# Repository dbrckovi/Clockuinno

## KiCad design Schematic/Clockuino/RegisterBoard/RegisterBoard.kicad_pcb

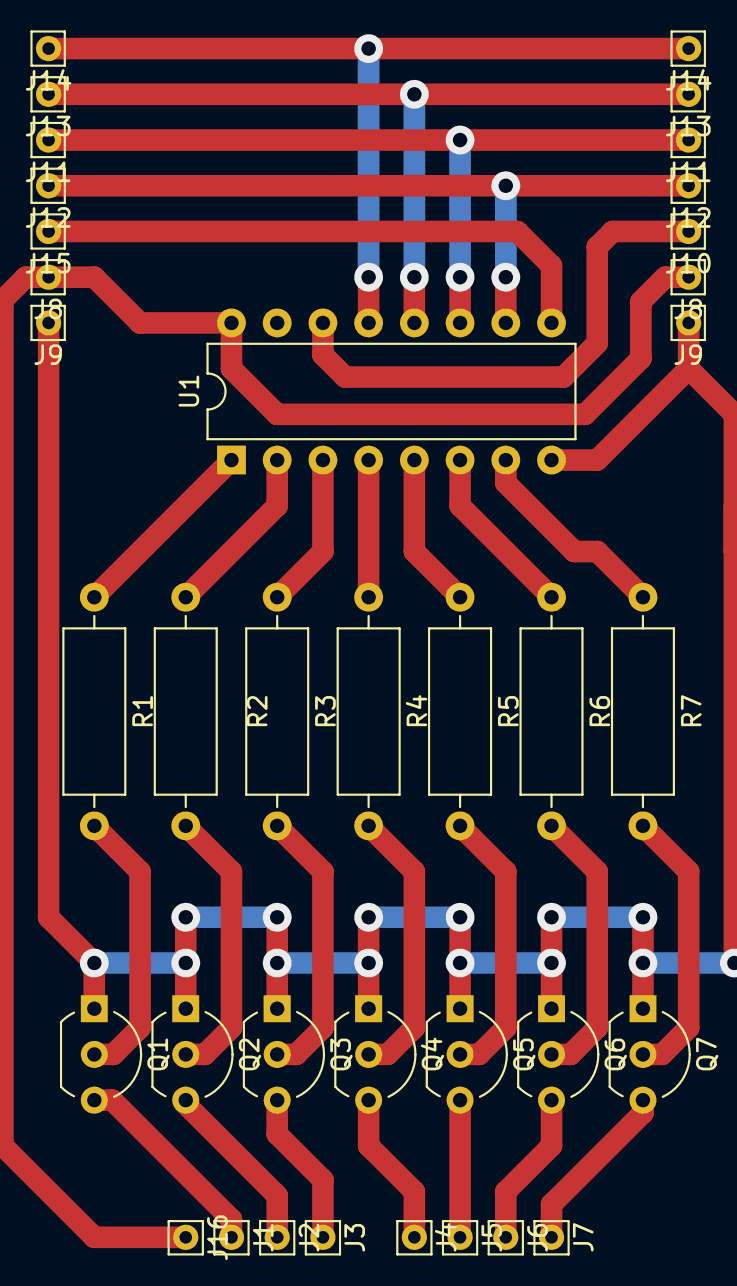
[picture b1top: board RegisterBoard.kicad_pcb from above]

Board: 2 copper layers, 37 parts (0 on the bottom side), 29 nets.

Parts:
J1, J2, J3, J4, J5, J6, J7: Conn_01x01_Pin; Pin_D0.7mm_L6.5mm_W1.8mm_FlatFork
J8, J8#2, J16: VCC +5; Pin_D0.7mm_L6.5mm_W1.8mm_FlatFork
J9, J9#2: GND; Pin_D0.7mm_L6.5mm_W1.8mm_FlatFork
J10: SER; Pin_D0.7mm_L6.5mm_W1.8mm_FlatFork
J11, J11#2: SRCLK; Pin_D0.7mm_L6.5mm_W1.8mm_FlatFork
J12, J12#2: SRCLR; Pin_D0.7mm_L6.5mm_W1.8mm_FlatFork
J13, J13#2: RCLK; Pin_D0.7mm_L6.5mm_W1.8mm_FlatFork
J14, J14#2: OE; Pin_D0.7mm_L6.5mm_W1.8mm_FlatFork
J15: NEXT; Pin_D0.7mm_L6.5mm_W1.8mm_FlatFork
Q1, Q2, Q3, Q4, Q5, Q6, Q7: 2N3904; TO-92_Inline_Wide
R1, R2, R3, R4, R5, R6, R7: R; R_Axial_DIN0309_L9.0mm_D3.2mm_P12.70mm_Horizontal
U1: 74AHCT595; DIP-16_W7.62mm

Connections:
unnamed: J1.1, Q1.3 (C)
unnamed: J2.1, Q2.3 (C)
unnamed: J3.1, Q3.3 (C)
unnamed: J4.1, Q4.3 (C)
unnamed: J5.1, Q5.3 (C)
unnamed: J6.1, Q6.3 (C)
unnamed: J7.1, Q7.3 (C)
unnamed: J9.1, J9#2.1, Q1.1 (E), Q2.1 (E), Q3.1 (E), Q4.1 (E), Q5.1 (E), Q6.1 (E), Q7.1 (E), U1.8 (GND)
unnamed: J10.1, U1.14 (SER)
unnamed: J11.1, J11#2.1, U1.11 (SRCLK)
unnamed: J12.1, J12#2.1, U1.10 (~SRCLR)
unnamed: J13.1, J13#2.1, U1.12 (RCLK)
unnamed: J14.1, J14#2.1, U1.13 (~OE)
unnamed: J15.1, U1.9 (QH')
unnamed: J8.1, J8#2.1, J16.1, U1.16 (VCC)
unnamed: Q1.2 (B), R1.2
unnamed: Q2.2 (B), R2.2
unnamed: Q3.2 (B), R3.2
unnamed: Q4.2 (B), R4.2
unnamed: Q5.2 (B), R5.2
unnamed: Q6.2 (B), R6.2
unnamed: Q7.2 (B), R7.2
unnamed: R1.1, U1.1 (QB)
unnamed: R2.1, U1.2 (QC)
unnamed: R3.1, U1.3 (QD)
unnamed: R4.1, U1.4 (QE)
unnamed: R5.1, U1.5 (QF)
unnamed: R6.1, U1.6 (QG)
unnamed: R7.1, U1.7 (QH)

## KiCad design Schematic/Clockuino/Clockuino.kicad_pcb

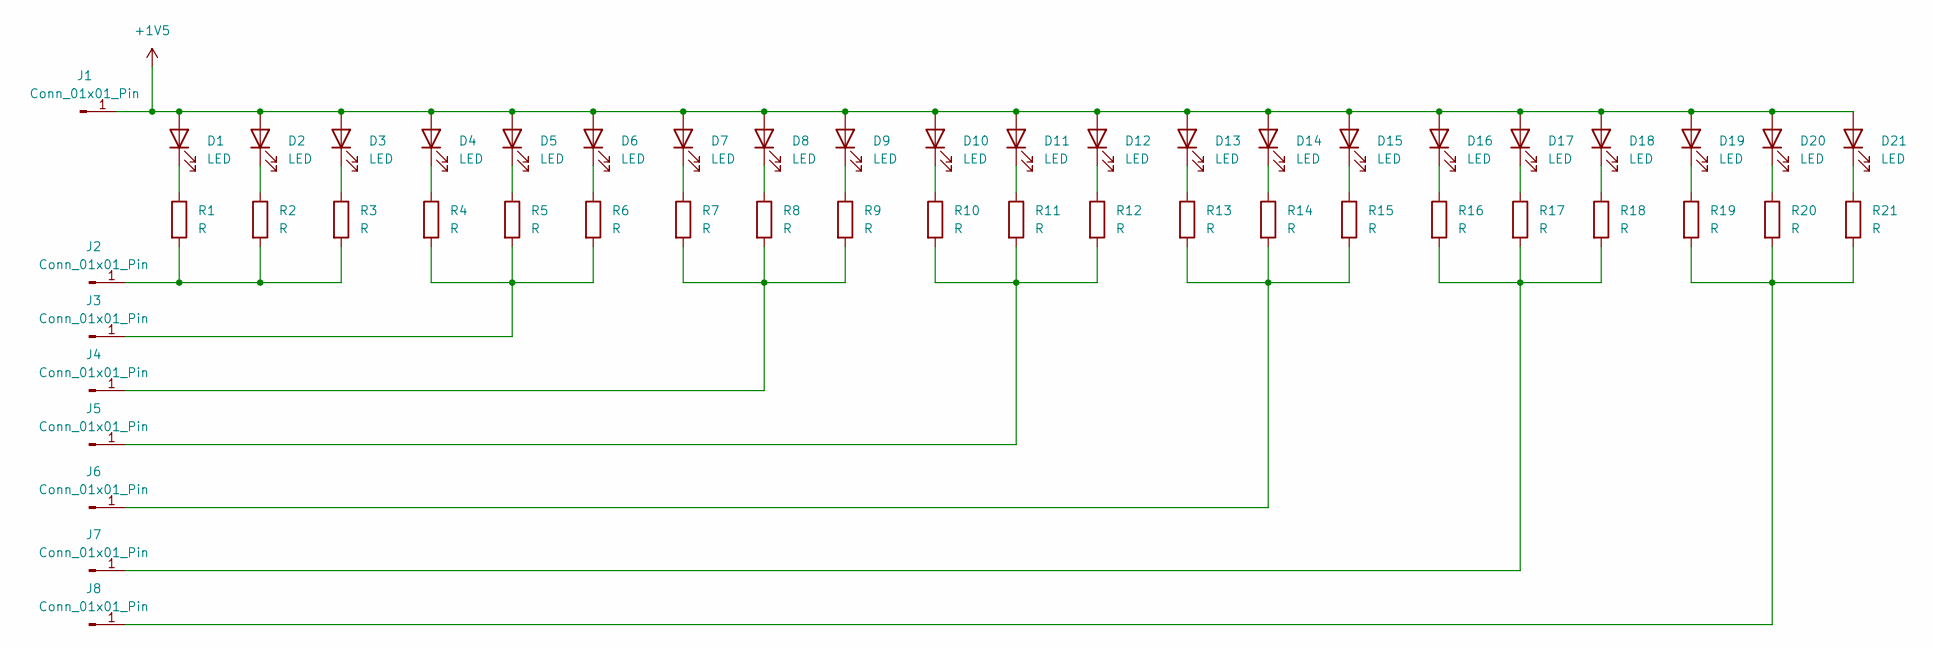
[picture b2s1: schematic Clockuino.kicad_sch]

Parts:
D1, D2, D3, D4, D5, D6, D7, D8, D9, D10, D11, D12, D13, D14, D15, D16, D17, D18, D19, D20, D21: LED; LED_D5.0mm
J1, J2, J3, J4, J5, J6, J7, J8: Conn_01x01_Pin; Pin_D1.0mm_L10.0mm
R1, R2, R3, R4, R5, R6, R10, R11, R12, R13, R14, R15, R19, R20, R21: R; R_Axial_DIN0204_L3.6mm_D1.6mm_P2.54mm_Vertical
R7, R8, R9, R16, R17, R18: R; R_Axial_DIN0204_L3.6mm_D1.6mm_P5.08mm_Horizontal

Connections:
+1V5: D1.2 (A), D2.2 (A), D3.2 (A), D4.2 (A), D5.2 (A), D6.2 (A), D7.2 (A), D8.2 (A), D9.2 (A), D10.2 (A), D11.2 (A), D12.2 (A), D13.2 (A), D14.2 (A), D15.2 (A), D16.2 (A), D17.2 (A), D18.2 (A), D19.2 (A), D20.2 (A), D21.2 (A), J1.1
unnamed: D1.1 (K), R1.1
unnamed: D2.1 (K), R2.1
unnamed: D3.1 (K), R3.1
unnamed: D4.1 (K), R4.1
unnamed: D5.1 (K), R5.1
unnamed: D6.1 (K), R6.1
unnamed: D7.1 (K), R7.1
unnamed: D8.1 (K), R8.1
unnamed: D9.1 (K), R9.1
unnamed: D10.1 (K), R10.1
unnamed: D11.1 (K), R11.1
unnamed: D12.1 (K), R12.1
unnamed: D13.1 (K), R13.1
unnamed: D14.1 (K), R14.1
unnamed: D15.1 (K), R15.1
unnamed: D16.1 (K), R16.1
unnamed: D17.1 (K), R17.1
unnamed: D18.1 (K), R18.1
unnamed: D19.1 (K), R19.1
unnamed: D20.1 (K), R20.1
unnamed: D21.1 (K), R21.1
unnamed: J2.1, R1.2, R2.2, R3.2
unnamed: J3.1, R4.2, R5.2, R6.2
unnamed: J4.1, R7.2, R8.2, R9.2
unnamed: J5.1, R10.2, R11.2, R12.2
unnamed: J6.1, R13.2, R14.2, R15.2
unnamed: J7.1, R16.2, R17.2, R18.2
unnamed: J8.1, R19.2, R20.2, R21.2

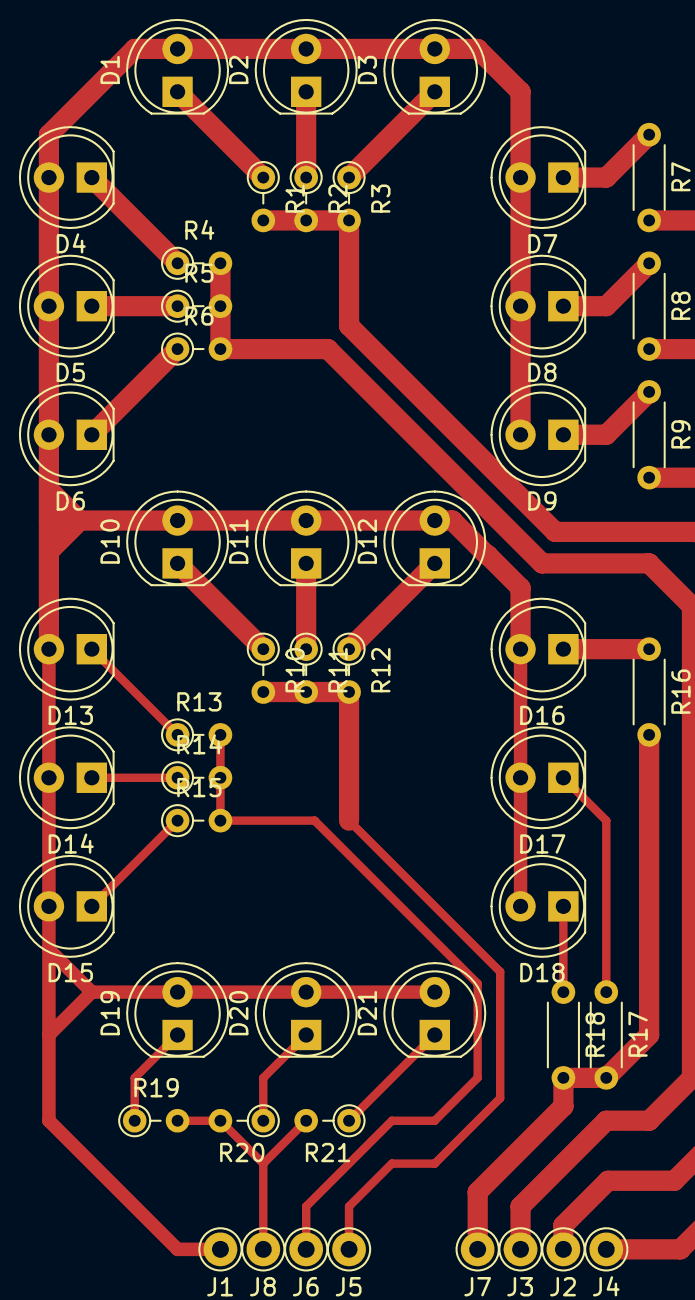
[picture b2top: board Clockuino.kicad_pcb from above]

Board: 2 copper layers, 50 parts (0 on the bottom side), 29 nets.

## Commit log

2024-03-24 Two segment display wiring
2024-03-25 Serialized two registers. Optimizations.
2024-05-02 Kicad schematic for led segment
2024-05-04 centered pins
2024-05-04 Deleted backups
2024-05-05 Laid down 6 resistors
2024-05-05 Shortened
2024-05-05 test
2024-05-05 del test
2024-05-23 Schematic and PCB for register boards
2024-06-01 Labels
2024-06-05 PCBS easier to make (not finished)(
